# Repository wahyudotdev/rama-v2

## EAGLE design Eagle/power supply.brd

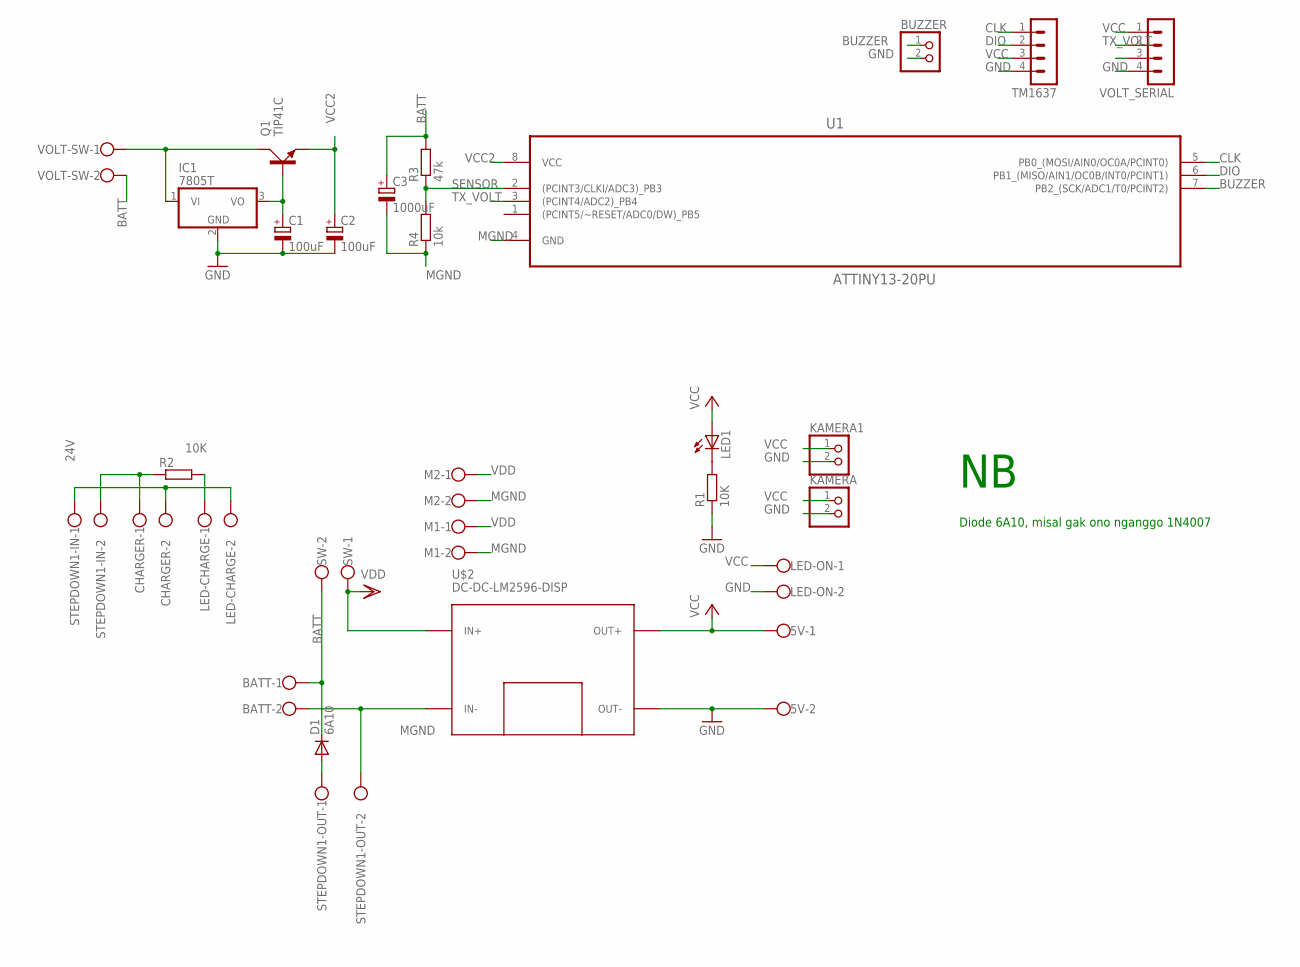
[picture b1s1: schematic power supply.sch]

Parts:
5V: W237-102
BATT: W237-102
BUZZER: PINHD-1X2; 1X02
C1, C2: 100uF; E2-4
C3: 1000uF; ETR4
CHARGER: W237-102
D1: 6A10; DO41-10
IC1: 7805T; TO220H
KAMERA, KAMERA1: PINHD-1X2; 1X02
LED1: LED5MM
LED-CHARGE: W237-102
LED-ON: W237-102
M1, M2: W237-102
Q1: TIP41C; TO220AV
R1: 10K; 0207/10
R2: 10K; 0617/22
R3: 47k; 0411/12
R4: 10k; 0411/12
STEPDOWN1-IN, STEPDOWN1-OUT: W237-102
SW: W237-102
TM1637: MA04-1
U1: ATTINY13-20PU; DIP254P762X533-8
U$2: DC-DC-LM2596-DISP
VOLT-SW: W237-102
VOLT_SERIAL: MA04-1

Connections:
24V: CHARGER.1, R2.1, STEPDOWN1-IN.2
BATT: BATT.1, C3.+, D1.C, R3.2, SW.2, VOLT-SW.2
BUZZER: BUZZER.1, U1.7 (PB2_(SCK/ADC1/T0/PCINT2))
CLK: TM1637.1, U1.5 (PB0_(MOSI/AIN0/OC0A/PCINT0))
DIO: TM1637.2, U1.6 (PB1_(MISO/AIN1/OC0B/INT0/PCINT1))
GND: 5V.2, BUZZER.2, C1.-, C2.-, IC1.2 (GND), KAMERA.2, KAMERA1.2, LED-ON.2, R1.1, TM1637.4, U$2.OUT-, VOLT_SERIAL.4
MGND: BATT.2, C3.-, M1.2, M2.2, R4.1, STEPDOWN1-OUT.2, U1.4 (GND), U$2.IN-
unnamed: C1.+, IC1.3 (VO), Q1.B
unnamed: IC1.1 (VI), Q1.C, VOLT-SW.1
unnamed: D1.A, STEPDOWN1-OUT.1
unnamed: LED1.K (C), R1.2
unnamed: CHARGER.2, LED-CHARGE.2, STEPDOWN1-IN.1
unnamed: LED-CHARGE.1, R2.2
SENSOR: R3.1, R4.2, U1.2 ((PCINT3/CLKI/ADC3)_PB3)
TX_VOLT: U1.3 ((PCINT4/ADC2)_PB4), VOLT_SERIAL.2
VCC: 5V.1, KAMERA.1, KAMERA1.1, LED1.A, LED-ON.1, TM1637.3, U$2.OUT+, VOLT_SERIAL.1
VCC2: C2.+, Q1.E, U1.8 (VCC)
VDD: M1.1, M2.1, SW.1, U$2.IN+

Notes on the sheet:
Diode 6A10, misal gak ono nganggo 1N4007

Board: 2 copper layers, 29 parts (0 on the bottom side), 18 nets, no tracks yet.

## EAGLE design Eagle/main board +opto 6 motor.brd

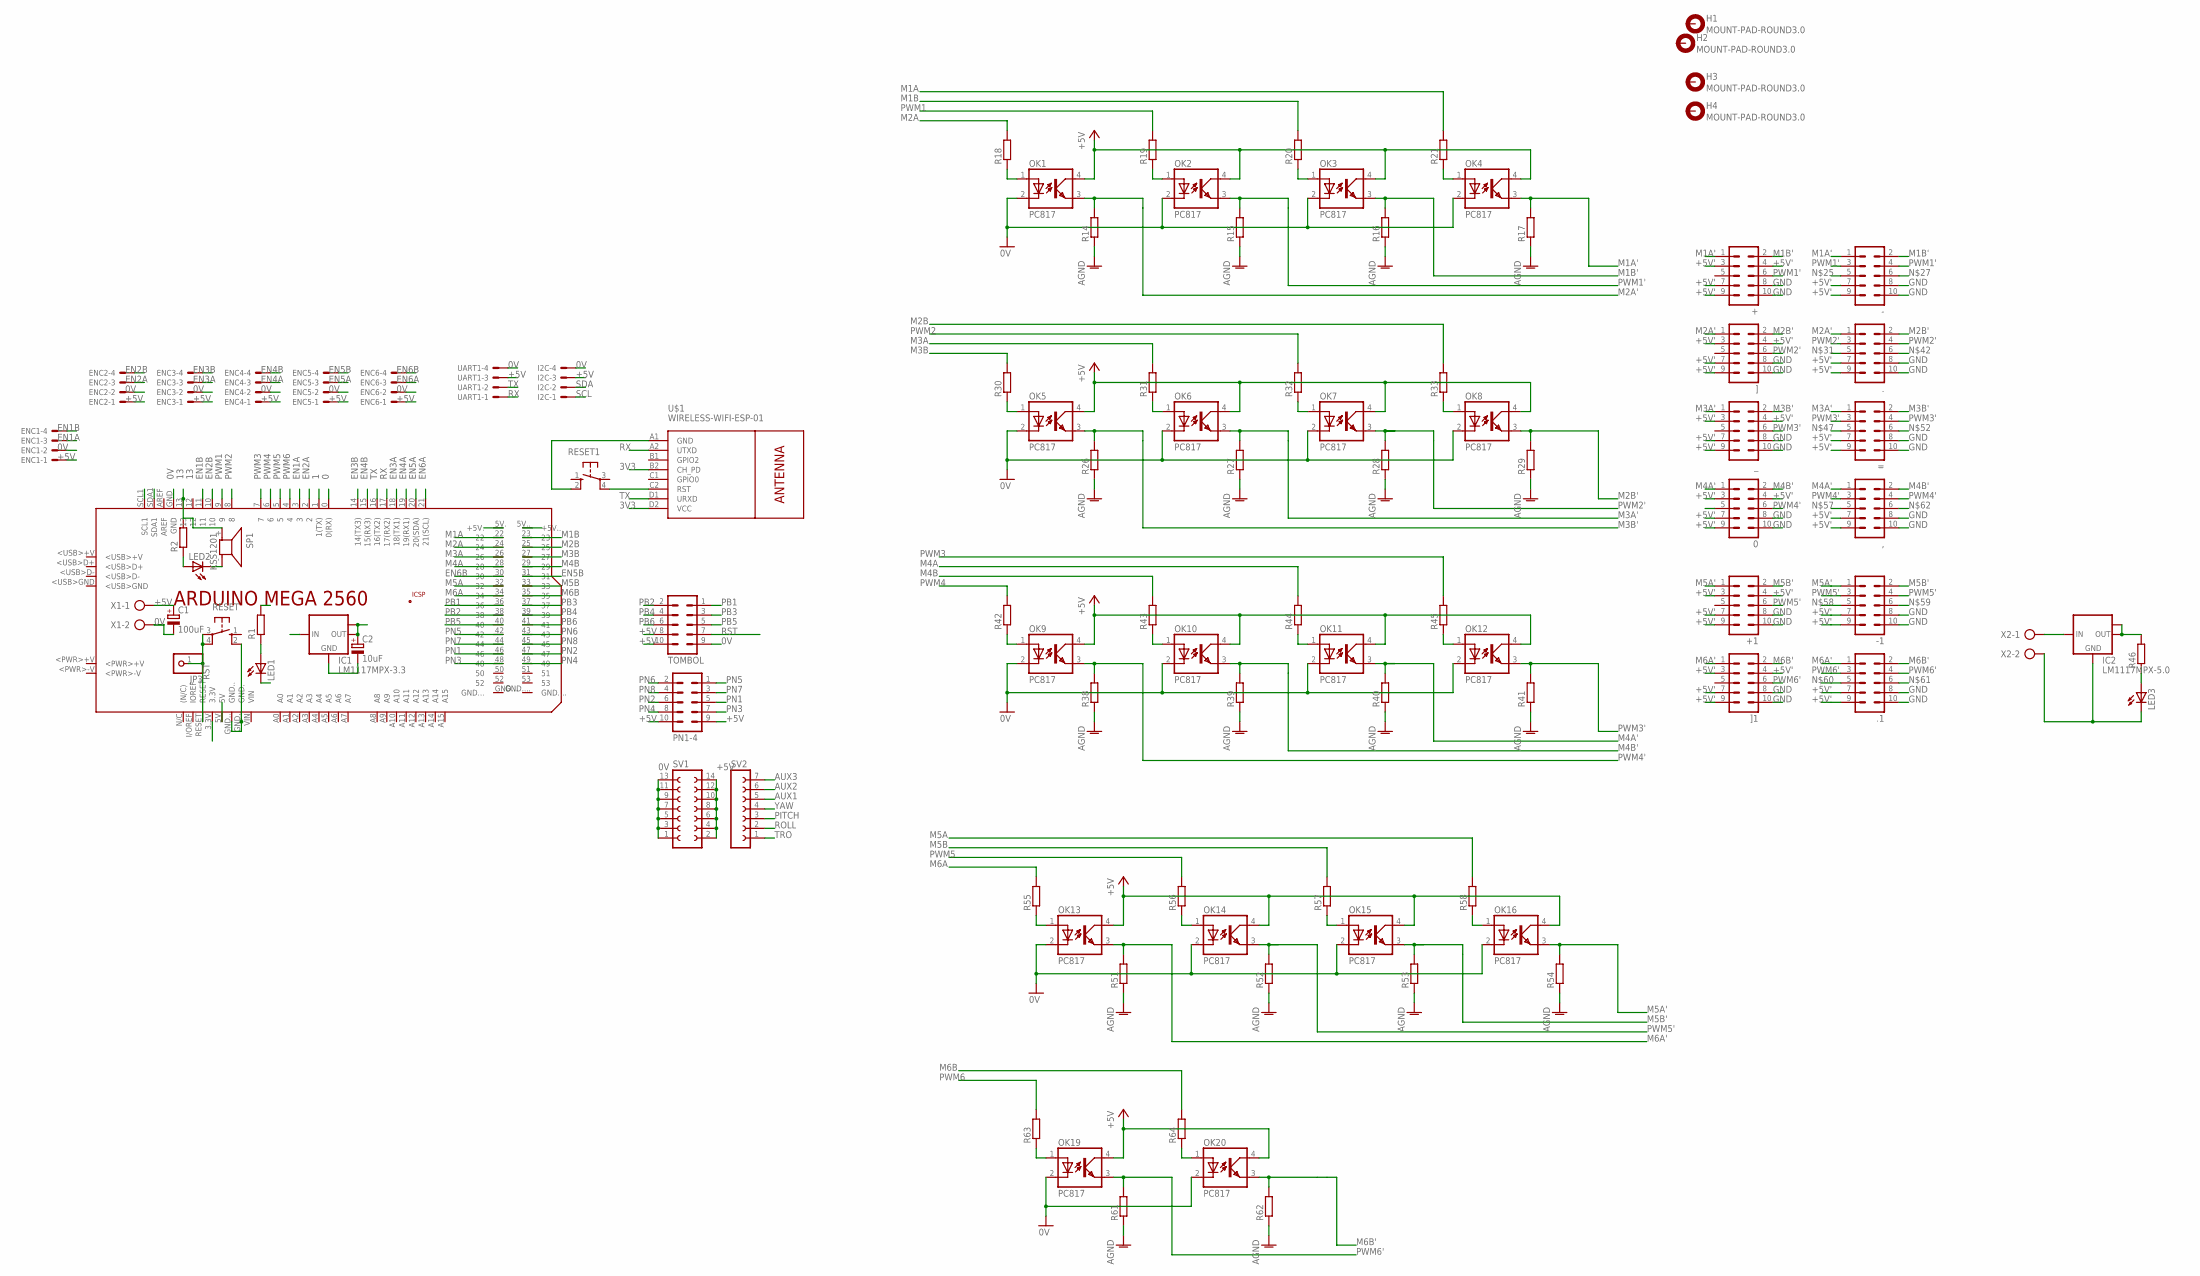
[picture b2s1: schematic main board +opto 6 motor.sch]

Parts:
0, ., .1: ML10
+, +1: ML10
,: ML10
-, -1: ML10
=: ML10
C1: 100uF; E2,5-5
C2: 10uF; E2,5-5
ENC1, ENC2, ENC3, ENC4, ENC5, ENC6: 22-23-2041
H1, H2, H3, H4: MOUNT-PAD-ROUND3.0; 3,0-PAD
I2C: 22-23-2041
IC1: LM1117MPX-3.3; SOT223
IC2: LM1117MPX-5.0; SOT223
JP3: PINHD-1X1; 1X01
LED1, LED2, LED3: LED3MM
OK1, OK2, OK3, OK4, OK5, OK6, OK7, OK8, OK9, OK10, OK11, OK12, OK13, OK14, OK15, OK16, OK19, OK20: PC817; DIL04
PCB1: ARDUINO_MEGA2560
PN1-4: ML10
R1, R2, R14, R15, R16, R17, R18, R19, R20, R21, R26, R27, R28, R29, R30, R31, R32, R33, R38, R39, R40, R41, R42, R43, R44, R45, R51, R52, R53, R54, R55, R56, R57, R58, R61, R62, R63, R64: R-EU_M0805; M0805
R46: R-EU_0207/10; 0207/10
RESET, RESET1: 40-XX; B3F-40XX
SP1: KSS1201
SV1: FE07-2
SV2: FE07-1; FE07
TOMBOL: ML10
U$1: WIRELESS-WIFI-ESP-01
UART1: 22-23-2041
X1: AK500/2
X2: AK300/2
], ]1: ML10
_: ML10

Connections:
0: PCB1.0 (0(RX))
0V: C1.-, ENC1.2, ENC2.2, ENC3.2, ENC4.2, ENC5.2, ENC6.2, I2C.4, LED1.K (C), LED2.K (C), OK1.2 (C), OK2.2 (C), OK3.2 (C), OK4.2 (C), OK5.2 (C), OK6.2 (C), OK7.2 (C), OK8.2 (C), OK9.2 (C), OK10.2 (C), OK11.2 (C), OK12.2 (C), OK13.2 (C), OK14.2 (C), OK15.2 (C), OK16.2 (C), OK19.2 (C), OK20.2 (C), PCB1.GND, PCB1.GND., PCB1.GND.., RESET.2 (S1), SP1.- (2), SV1.1, SV1.3, SV1.5, SV1.7, SV1.9, SV1.11, SV1.13, TOMBOL.9, UART1.4, X1.2
1: PCB1.1 (1(TX))
3V3: C2.+, IC1.2 (OUT), IC1.TAB (OUT1), PCB1.3.3V, U$1.B2 (CH_PD), U$1.D2 (VCC)
13: PCB1.13, R2.2, SP1.+ (1)
+5V: C1.+, ENC1.1, ENC2.1, ENC3.1, ENC4.1, ENC5.1, ENC6.1, I2C.3, IC1.3 (IN), PCB1.5V, PCB1.5V. (+5V.), PCB1.5V.. (+5V..), PN1-4.9, PN1-4.10, R1.2, SV1.2, SV1.4, SV1.6, SV1.8, SV1.10, SV1.12, SV1.14, TOMBOL.8, TOMBOL.10, UART1.3, X1.1
+5V': 0.3, 0.4, 0.7, 0.9, +.3, +.4, +.7, +.9, +1.3, +1.4, +1.7, +1.9, ,.7, ,.9, -.7, -.9, -1.7, -1.9, ..7, ..9, .1.7, .1.9, =.7, =.9, IC2.2 (OUT), IC2.TAB (OUT1), OK1.4 (COL), OK2.4 (COL), OK3.4 (COL), OK4.4 (COL), OK5.4 (COL), OK6.4 (COL), OK7.4 (COL), OK8.4 (COL), OK9.4 (COL), OK10.4 (COL), OK11.4 (COL), OK12.4 (COL), OK13.4 (COL), OK14.4 (COL), OK15.4 (COL), OK16.4 (COL), OK19.4 (COL), OK20.4 (COL), R46.2, ].3, ].4, ].7, ].9, ]1.3, ]1.4, ]1.7, ]1.9, _.3, _.4, _.7, _.9
AUX1: SV2.5
AUX2: SV2.6
AUX3: SV2.7
EN1A: ENC1.3, PCB1.3
EN1B: ENC1.4, PCB1.11
EN2A: ENC2.3, PCB1.2
EN2B: ENC2.4, PCB1.10
EN3A: ENC3.3, PCB1.18 (18(TX1))
EN3B: ENC3.4, PCB1.14 (14(TX3))
EN4A: ENC4.3, PCB1.19 (19(RX1))
EN4B: ENC4.4, PCB1.15 (15(RX3))
EN5A: ENC5.3, PCB1.20 (20(SDA))
EN5B: ENC5.4, PCB1.31
EN6A: ENC6.3, PCB1.21 (21(SCL))
EN6B: ENC6.4, PCB1.30
GND: 0.8, 0.10, +.8, +.10, +1.8, +1.10, ,.8, ,.10, -.8, -.10, -1.8, -1.10, ..8, ..10, .1.8, .1.10, =.8, =.10, IC2.1 (GND), LED3.K (C), R14.1, R15.1, R16.1, R17.1, R26.1, R27.1, R28.1, R29.1, R38.1, R39.1, R40.1, R41.1, R51.1, R52.1, R53.1, R54.1, R61.1, R62.1, X2.2, ].8, ].10, ]1.8, ]1.10, _.8, _.10
M1A: PCB1.22, R21.2
M1A': +.1, -.1, OK4.3 (EMIT), R17.2
M1B: PCB1.23, R20.2
M1B': +.2, -.2, OK3.3 (EMIT), R16.2
M2A: PCB1.24, R18.2
M2A': ..1, OK1.3 (EMIT), R14.2, ].1
M2B: PCB1.25, R33.2
M2B': ..2, OK8.3 (EMIT), R29.2, ].2
M3A: PCB1.26, R31.2
M3A': =.1, OK6.3 (EMIT), R27.2, _.1
M3B: PCB1.27, R30.2
M3B': =.2, OK5.3 (EMIT), R26.2, _.2
M4A: PCB1.28, R44.2
M4A': 0.1, ,.1, OK11.3 (EMIT), R40.2
M4B: PCB1.29, R43.2
M4B': 0.2, ,.2, OK10.3 (EMIT), R39.2
M5A: PCB1.32, R58.2
M5A': +1.1, -1.1, OK16.3 (EMIT), R54.2
M5B: PCB1.33, R57.2
M5B': +1.2, -1.2, OK15.3 (EMIT), R53.2
M6A: PCB1.34, R55.2
M6A': .1.1, OK13.3 (EMIT), R51.2, ]1.1
M6B: PCB1.35, R64.2
M6B': .1.2, OK20.3 (EMIT), R62.2, ]1.2
unnamed: RESET1.2 (S1), U$1.A1 (GND)
unnamed: LED1.A, R1.1
unnamed: LED2.A, R2.1
unnamed: C2.-, IC1.1 (GND)
unnamed: OK1.1 (A), R18.1
unnamed: OK2.1 (A), R19.1
unnamed: OK3.1 (A), R20.1
unnamed: OK4.1 (A), R21.1
unnamed: RESET1.4 (P1), U$1.C2 (RST)
unnamed: OK5.1 (A), R30.1
unnamed: OK6.1 (A), R31.1
unnamed: OK7.1 (A), R32.1
unnamed: OK8.1 (A), R33.1
unnamed: LED3.A, R46.1
unnamed: IC2.3 (IN), X2.1
unnamed: OK9.1 (A), R42.1
unnamed: OK10.1 (A), R43.1
unnamed: OK11.1 (A), R44.1
unnamed: OK12.1 (A), R45.1
unnamed: OK13.1 (A), R55.1
unnamed: OK14.1 (A), R56.1
unnamed: OK15.1 (A), R57.1
unnamed: OK16.1 (A), R58.1
unnamed: OK19.1 (A), R63.1
unnamed: OK20.1 (A), R64.1
NC4: 0.5
PB1: PCB1.36, TOMBOL.1
PB2: PCB1.38, TOMBOL.2
PB3: PCB1.37, TOMBOL.3
PB4: PCB1.39, TOMBOL.4
PB5: PCB1.40, TOMBOL.5
PB6: PCB1.41, TOMBOL.6
PITCH: SV2.3
PN1: PCB1.46, PN1-4.5
PN2: PCB1.47, PN1-4.6
PN3: PCB1.48, PN1-4.7
PN4: PCB1.49, PN1-4.8
PN5: PCB1.42, PN1-4.1
PN6: PCB1.43, PN1-4.2
PN7: PCB1.44, PN1-4.3
PN8: PCB1.45, PN1-4.4
PWM1: PCB1.9, R19.2
PWM1': +.6, -.3, -.4, OK2.3 (EMIT), R15.2
PWM2: PCB1.8, R32.2
PWM2': ..3, ..4, OK7.3 (EMIT), R28.2, ].6
PWM3: PCB1.7, R45.2
PWM3': =.3, =.4, OK12.3 (EMIT), R41.2, _.6
PWM4: PCB1.6, R42.2
PWM4': 0.6, ,.3, ,.4, OK9.3 (EMIT), R38.2
PWM5: PCB1.5, R56.2
PWM5': +1.6, -1.3, -1.4, OK14.3 (EMIT), R52.2
PWM6: PCB1.4, R63.2
PWM6': .1.3, .1.4, OK19.3 (EMIT), R61.2, ]1.6
ROLL: SV2.2
RST: JP3.1, PCB1.RESET, RESET.3, RESET.4 (P1), TOMBOL.7
RX: PCB1.17 (17(RX2)), U$1.A2 (UTXD), UART1.1
SCL: I2C.1, PCB1.SCL1
SDA: I2C.2, PCB1.SDA1
TRO: SV2.1
TX: PCB1.16 (16(TX2)), U$1.D1 (URXD), UART1.2
YAW: SV2.4

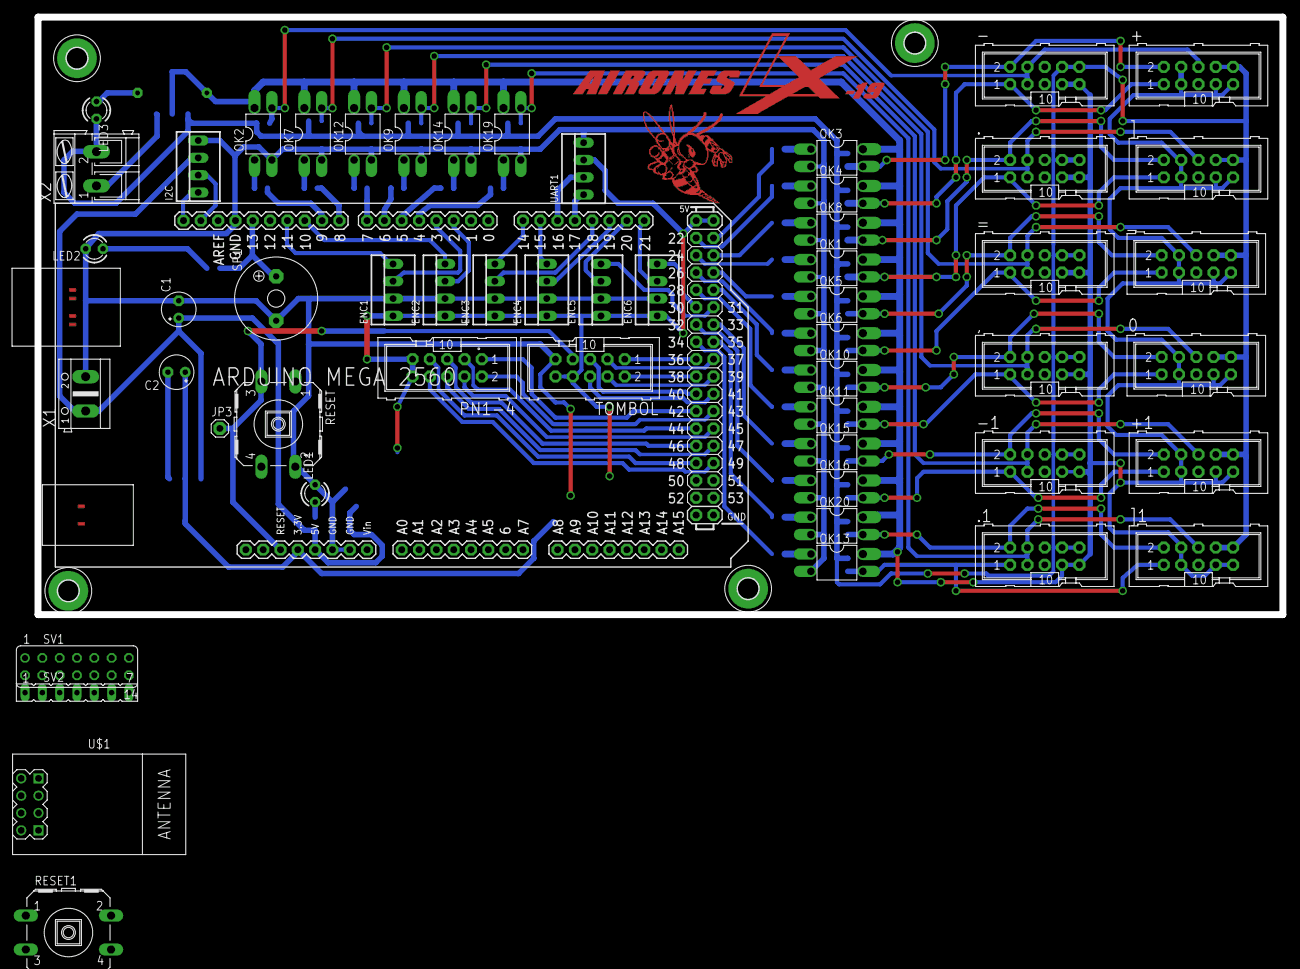
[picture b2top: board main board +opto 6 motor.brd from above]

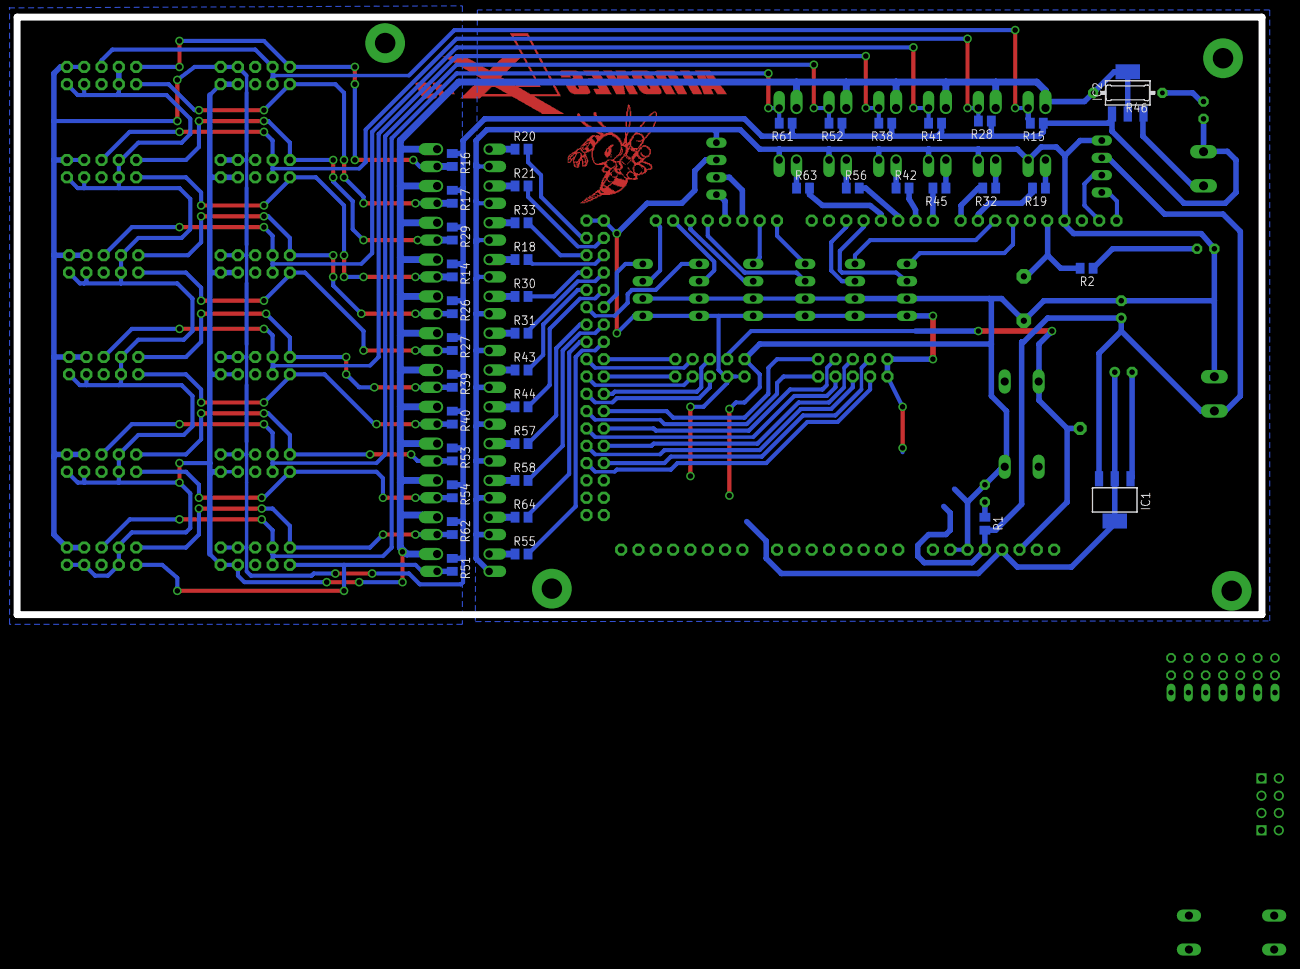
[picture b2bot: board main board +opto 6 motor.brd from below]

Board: 2 copper layers, 182.6 x 87.6 mm, 100 parts (41 on the bottom side), 98 nets.

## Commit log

2020-10-23 ESP MQTT logger
2020-10-25 library motor + library kinematic wes bar
2020-11-01 wes bar kih iso mlaku bismillah
2020-11-08 mbuh gek error
2020-11-08 bismillah sangar
2020-11-11 bismillah sangar 11 nov 2020
2020-11-11 test mqtt ESP-01 done
2020-11-12 edit servo write method, add exmitter connected variable
2020-11-12 added mqtt data receiver with mysql
2020-11-17 fix kinematic roda 2, fix logic
2020-11-17 fix remote direction
2020-12-02 fix arah
2020-12-05 add pwm change
2020-12-06 remove serial flush, fix rotate
2021-01-04 add joystick, mqtt
2021-01-15 add smart wifi connect
2021-01-16 basic functionality done
2021-01-16 added master slave due esp-01
2021-01-16 fix reconnecting error
2021-01-26 rama desktop controller with video and mqtt support
2021-01-27 folder structure
2021-01-27 added power supply schematic
2021-01-27 change gitignore
2021-02-02 add ESP32 cam + get IP via mqtt
2021-02-07 clean arch
2021-02-07 added user interface for ultrasonic data
2021-02-07 add doc
2021-02-08 added speed slider
2021-02-10 remove speed bar
2021-02-13 added UDP stream server
2021-02-13 added udp stream class
2021-02-13 fix path
2021-02-14 added connection status
2021-02-14 add speed control
2021-02-19 fix key press down<>left
2021-02-19 mbenerke pwm
2021-02-21 fix camera rotation
2021-02-21 fix motor speed
2021-02-21 fix requierement.txt
2021-02-22 updated documentation
2021-06-04 cleaning code
2021-10-02 fix library
2021-11-10 Added flowchart_rama
2021-11-10 Update flowchart_rama

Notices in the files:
parts and their libraries:
ESP-01: Released under the Creative Commons Attribution 4.0 International License: http://creativecommons.org/licenses/by/4.0
